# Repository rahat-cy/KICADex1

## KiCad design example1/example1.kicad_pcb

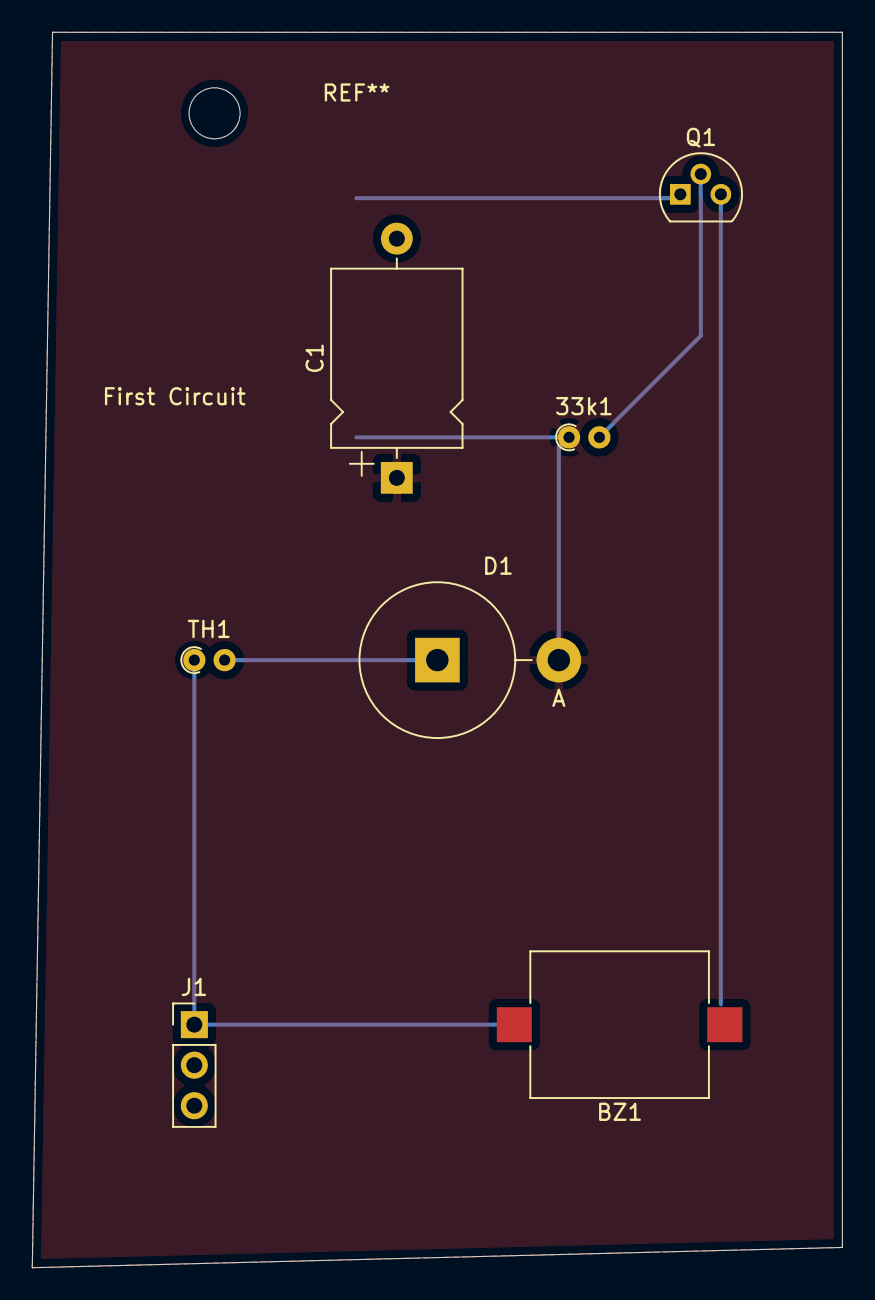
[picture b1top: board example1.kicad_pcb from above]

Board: 2 copper layers, 50.8 x 77.5 mm, 7 parts (0 on the bottom side), 6 nets.

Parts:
33k1: R; R_Axial_DIN0204_L3.6mm_D1.6mm_P1.90mm_Vertical
BZ1: Buzzer; Buzzer_Mallory_AST1109MLTRQ
C1: 10uF; CP_Axial_L11.0mm_D8.0mm_P15.00mm_Horizontal
D1: 1N4007; D_5KP_P7.62mm_Vertical_AnodeUp
J1: Conn_01x03_Male; PinHeader_1x03_P2.54mm_Vertical
Q1: 2N2219; TO-92L
TH1: 5k; R_Axial_DIN0204_L3.6mm_D1.6mm_P1.90mm_Vertical

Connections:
unnamed: 33k1.1, C1.1, D1.2
unnamed: 33k1.2, Q1.2
unnamed: BZ1.1, J1.1, TH1.1
unnamed: BZ1.2, Q1.3
unnamed: C1.2, Q1.1
unnamed: D1.1, TH1.2

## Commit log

2021-09-29 add example 1
2021-10-06 My First Commit
2021-10-06 My Second Commit
